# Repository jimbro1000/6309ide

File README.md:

# 8 Bit IDE for 6309 SBC #

Inspired (and partially copied from) Breadbording Labs 
(https://www.youtube.com/@breadboardinglabs) which is,
in turn, taken from other existing 8 bit IDE projects.

This design is configured to work with my 6309 SBC 
project.

## Status ##

This is a work in progress and is not ready for production.
The two SEL lines are not wired and need some address selection
logic to fit the design to the available mapped memory

## Drivers ##

The IDE operation requires software drivers to simplify
operation. It also needs programming for the GAL

### GAL Definition ###

Input (1-9):  
A0, A4, A5, A6, A6, E, SEL0, RW, SEL1

Output (19-12):  
!UDW, !UDR, !LDW, !IOW, !IOR, !CS0, !CS1, !LDR

ACT = !A5 & !A6 & !A7 & !SEL0

CS0 = !A4 & ACT  
CS1 = A4 & ACT  
IOR = !A0 & ACT & RW  
IOW = A0 & ACT & !RW  
LDR = !A0 & ACT & RW  
LDW = !A0 & ACT & !RW  
UDR = A0 & ACT & RW  
UDW = A0 & ACT & !RW

(note: IOR and LDR are the same)

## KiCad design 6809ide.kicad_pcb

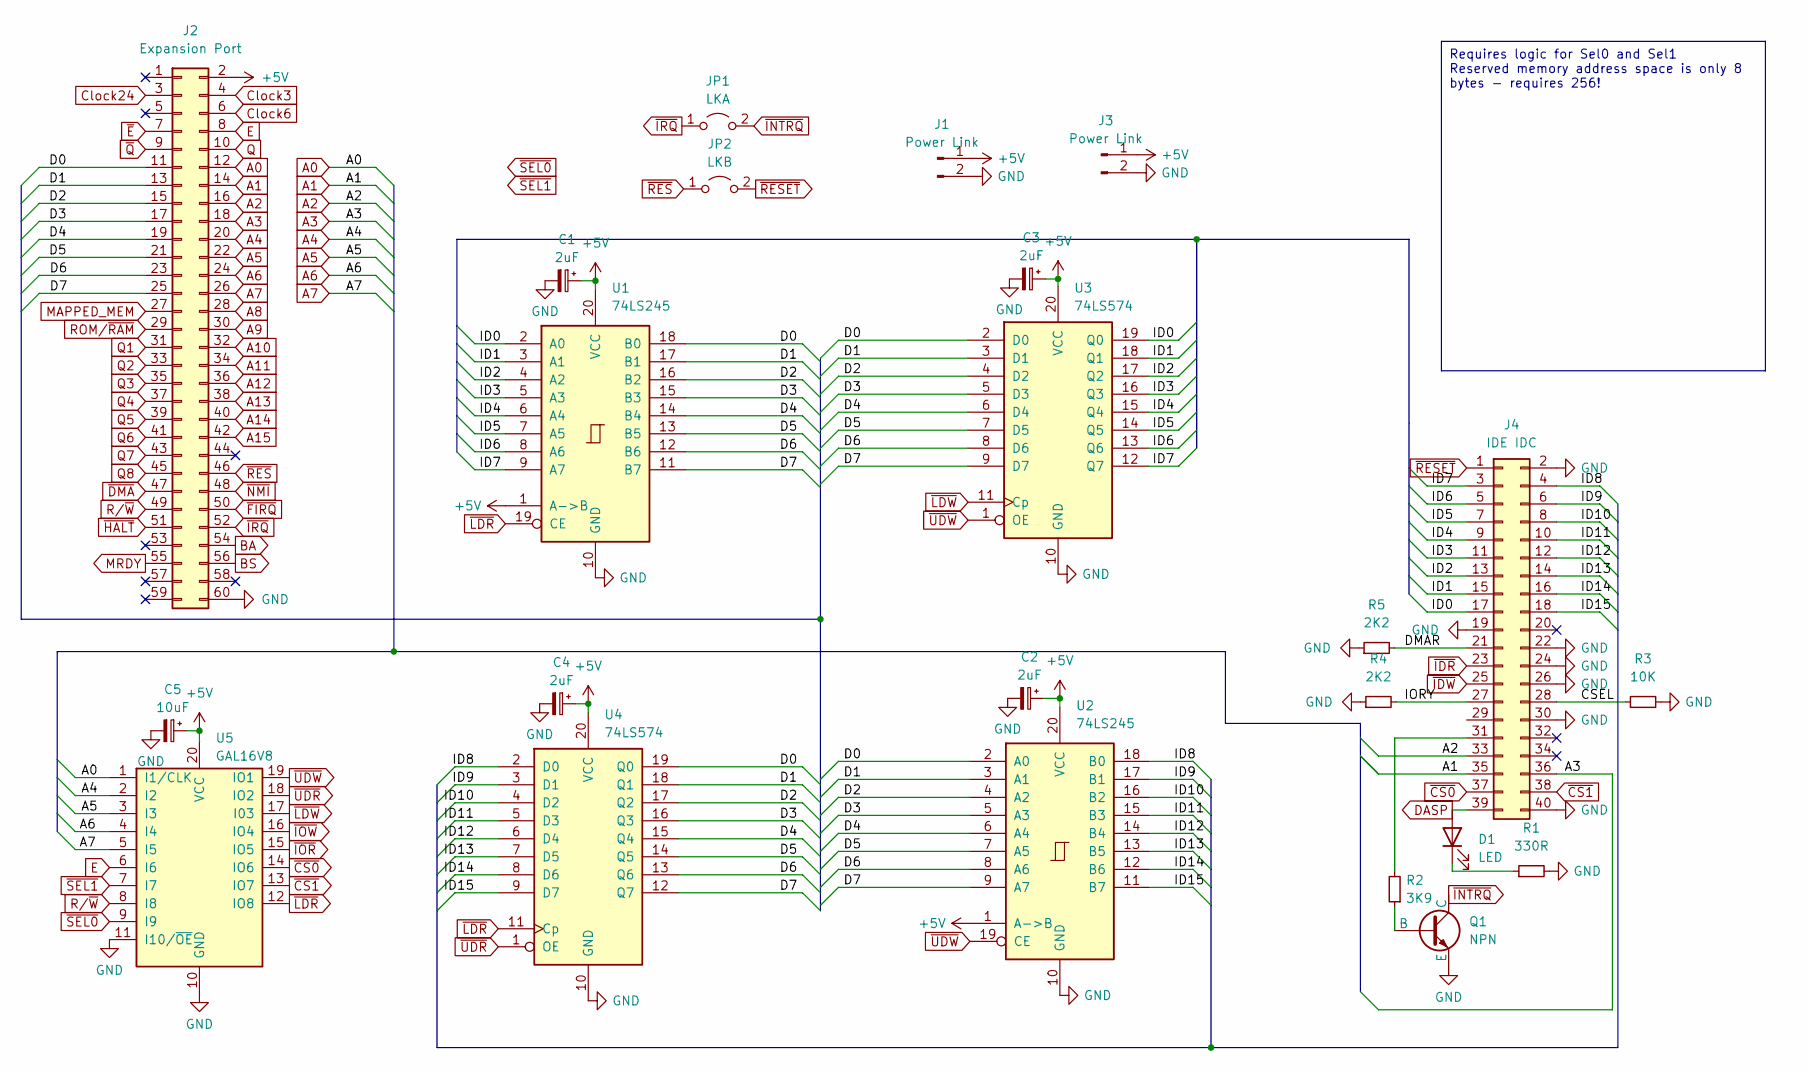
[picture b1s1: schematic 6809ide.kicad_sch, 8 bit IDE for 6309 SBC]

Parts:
C1, C2, C3, C4: 2uF; CP_Elec_4x3
C5: 10uF; CP_Elec_6.3x3
D1: LED; LED_0805_2012Metric_Pad1.15x1.40mm_HandSolder
J1, J3: Power Link; PinHeader_1x02_P2.54mm_Vertical
J2: Expansion Port; PinHeader_2x30_P2.54mm_Vertical
J4: IDE IDC; IDC-Header_2x20_P2.54mm_Vertical
JP1: LKA; SolderJumper-2_P1.3mm_Open_RoundedPad1.0x1.5mm
JP2: LKB; SolderJumper-2_P1.3mm_Open_RoundedPad1.0x1.5mm
Q1: NPN; SOT-23-3
R1: 330R; R_0805_2012Metric_Pad1.20x1.40mm_HandSolder
R2: 3K9; R_0805_2012Metric_Pad1.20x1.40mm_HandSolder
R3: 10K; R_0805_2012Metric_Pad1.20x1.40mm_HandSolder
R4, R5: 2K2; R_0805_2012Metric_Pad1.20x1.40mm_HandSolder
U1, U2: 74LS245; SOIC-20W_7.5x12.8mm_P1.27mm
U3, U4: 74LS574; SOIC-20W_7.5x12.8mm_P1.27mm
U5: GAL16V8; SOIC-20W_7.5x12.8mm_P1.27mm

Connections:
+5V: C1.1, C2.1, C3.1, C4.1, C5.1, J1.1, J2.2, J3.1, U1.1 (A->B), U1.20 (VCC), U2.1 (A->B), U2.20 (VCC), U3.20 (VCC), U4.20 (VCC), U5.20 (VCC)
/CSEL: J4.28, R3.1
/D0: J2.11, U1.18 (B0), U2.2 (A0), U3.2 (D0), U4.19 (Q0)
/D1: J2.13, U1.17 (B1), U2.3 (A1), U3.3 (D1), U4.18 (Q1)
/D2: J2.15, U1.16 (B2), U2.4 (A2), U3.4 (D2), U4.17 (Q2)
/D3: J2.17, U1.15 (B3), U2.5 (A3), U3.5 (D3), U4.16 (Q3)
/D4: J2.19, U1.14 (B4), U2.6 (A4), U3.6 (D4), U4.15 (Q4)
/D5: J2.21, U1.13 (B5), U2.7 (A5), U3.7 (D5), U4.14 (Q5)
/D6: J2.23, U1.12 (B6), U2.8 (A6), U3.8 (D6), U4.13 (Q6)
/D7: J2.25, U1.11 (B7), U2.9 (A7), U3.9 (D7), U4.12 (Q7)
/DMAR: J4.21, R5.2
/ID0: J4.17, U1.2 (A0), U3.19 (Q0)
/ID1: J4.15, U1.3 (A1), U3.18 (Q1)
/ID2: J4.13, U1.4 (A2), U3.17 (Q2)
/ID3: J4.11, U1.5 (A3), U3.16 (Q3)
/ID4: J4.9, U1.6 (A4), U3.15 (Q4)
/ID5: J4.7, U1.7 (A5), U3.14 (Q5)
/ID6: J4.5, U1.8 (A6), U3.13 (Q6)
/ID7: J4.3, U1.9 (A7), U3.12 (Q7)
/ID8: J4.4, U2.18 (B0), U4.2 (D0)
/ID9: J4.6, U2.17 (B1), U4.3 (D1)
/ID10: J4.8, U2.16 (B2), U4.4 (D2)
/ID11: J4.10, U2.15 (B3), U4.5 (D3)
/ID12: J4.12, U2.14 (B4), U4.6 (D4)
/ID13: J4.14, U2.13 (B5), U4.7 (D5)
/ID14: J4.16, U2.12 (B6), U4.8 (D6)
/ID15: J4.18, U2.11 (B7), U4.9 (D7)
/IORY: J4.27, R4.2
A0: J2.12, U5.1 (I1/CLK)
A1: J2.14, J4.35
A2: J2.16, J4.33
A3: J2.18, J4.36
A4: J2.20, U5.2 (I2)
A5: J2.22, U5.3 (I3)
A6: J2.24, U5.4 (I4)
A7: J2.26, U5.5 (I5)
A8: J2.28
A9: J2.30
A10: J2.32
A11: J2.34
A12: J2.36
A13: J2.38
A14: J2.40
A15: J2.42
BA: J2.54
BS: J2.56
Clock3: J2.4
Clock6: J2.6
Clock24: J2.3
DASP: D1.2 (A), J4.39
E: J2.8, U5.6 (I6)
GND: C1.2, C2.2, C3.2, C4.2, C5.2, J1.2, J2.60, J3.2, J4.2, J4.19, J4.22, J4.24, J4.26, J4.30, J4.40, Q1.3 (E), R1.2, R3.2, R4.1, R5.1, U1.10 (GND), U2.10 (GND), U3.10 (GND), U4.10 (GND), U5.10 (GND), U5.11 (I10/~OE)
MAPPED_MEM: J2.27
MRDY: J2.55
unnamed: D1.1 (K), R1.1
unnamed: J4.31, R2.2
unnamed: Q1.2 (B), R2.1
Q: J2.10
Q1: J2.31
Q2: J2.33
Q3: J2.35
Q4: J2.37
Q5: J2.39
Q6: J2.41
Q7: J2.43
Q8: J2.45
ROM/~RAM: J2.29
R/~W: J2.49, U5.8 (I8)
~CS0: J4.37, U5.14 (IO6)
~CS1: J4.38, U5.13 (IO7)
~DMA: J2.47
~E: J2.7
~FIRQ: J2.50
~HALT: J2.51
~IDR: J4.23
~IDW: J4.25
~INTRQ: JP1.2 (B), Q1.1 (C)
~IOR: U5.15 (IO5)
~IOW: U5.16 (IO4)
~IRQ: J2.52, JP1.1 (A)
~LDR: U1.19 (CE), U4.11 (Cp), U5.12 (IO8)
~LDW: U3.11 (Cp), U5.17 (I03)
~NMI: J2.48
~Q: J2.9
~RESET: J4.1, JP2.2 (B)
~RES: J2.46, JP2.1 (A)
~SEL0: U5.9 (I9)
~SEL1: U5.7 (I7)
~UDR: U4.1 (OE), U5.18 (IO2)
~UDW: U2.19 (CE), U3.1 (OE), U5.19 (IO1)

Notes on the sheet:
Requires logic for Sel0 and Sel1 Reserved memory address space is only 8 bytes - requires 256!

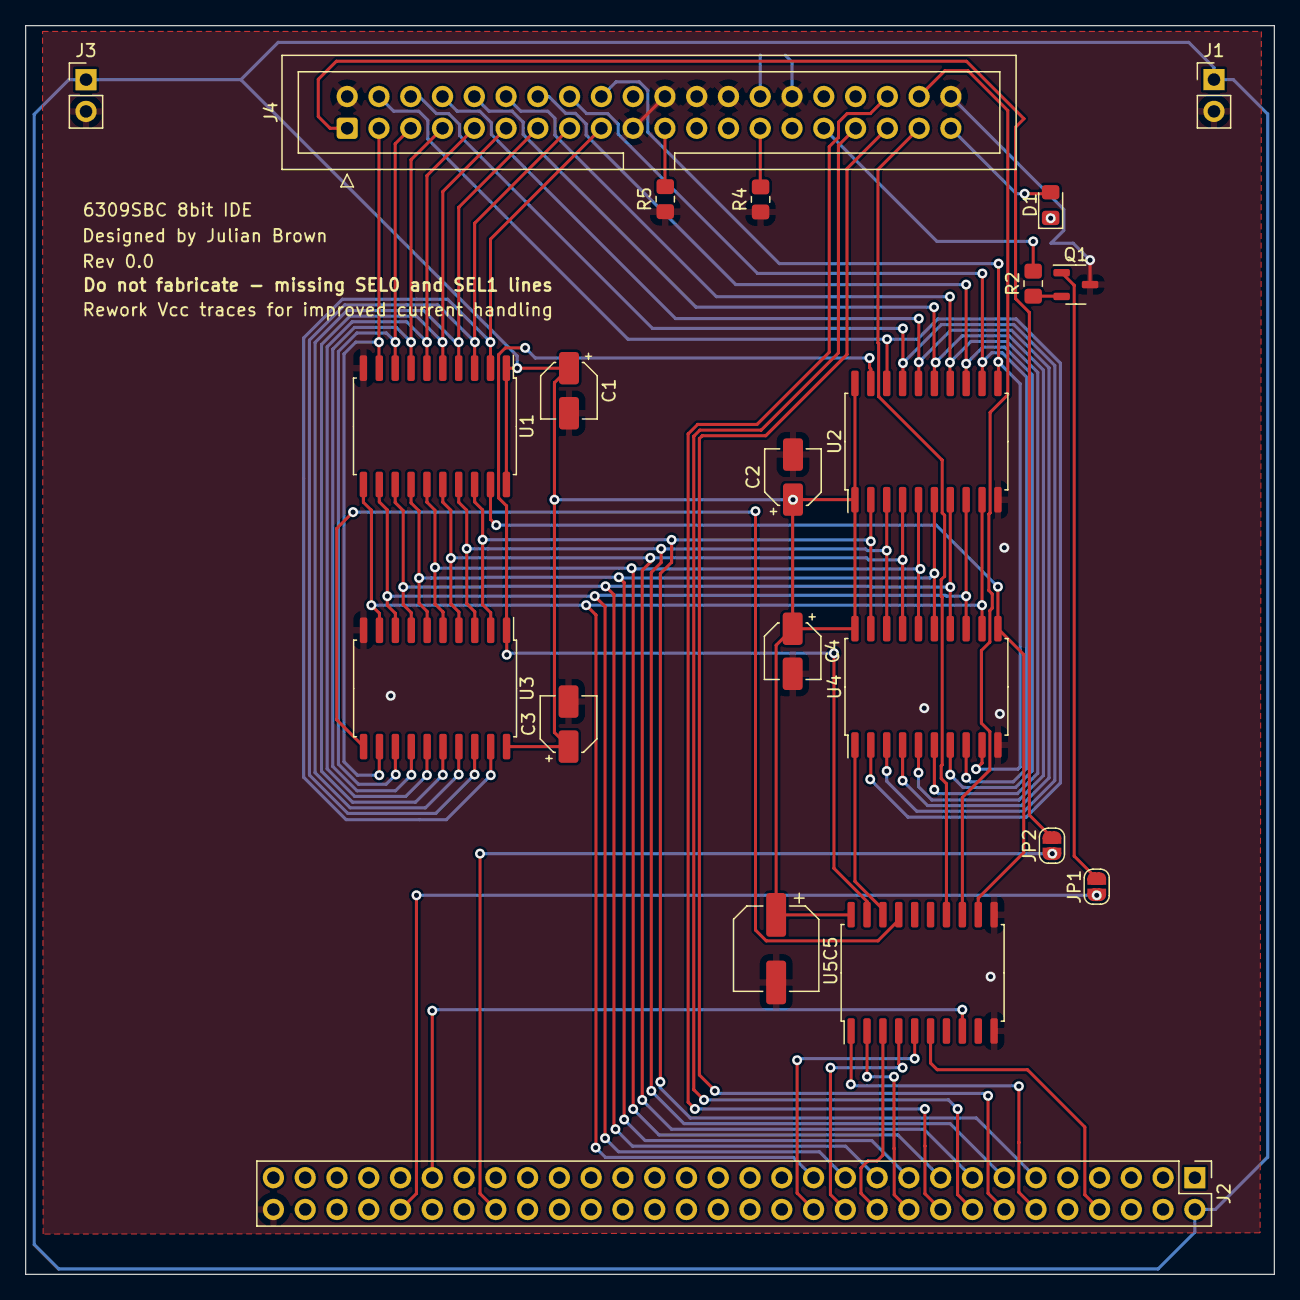
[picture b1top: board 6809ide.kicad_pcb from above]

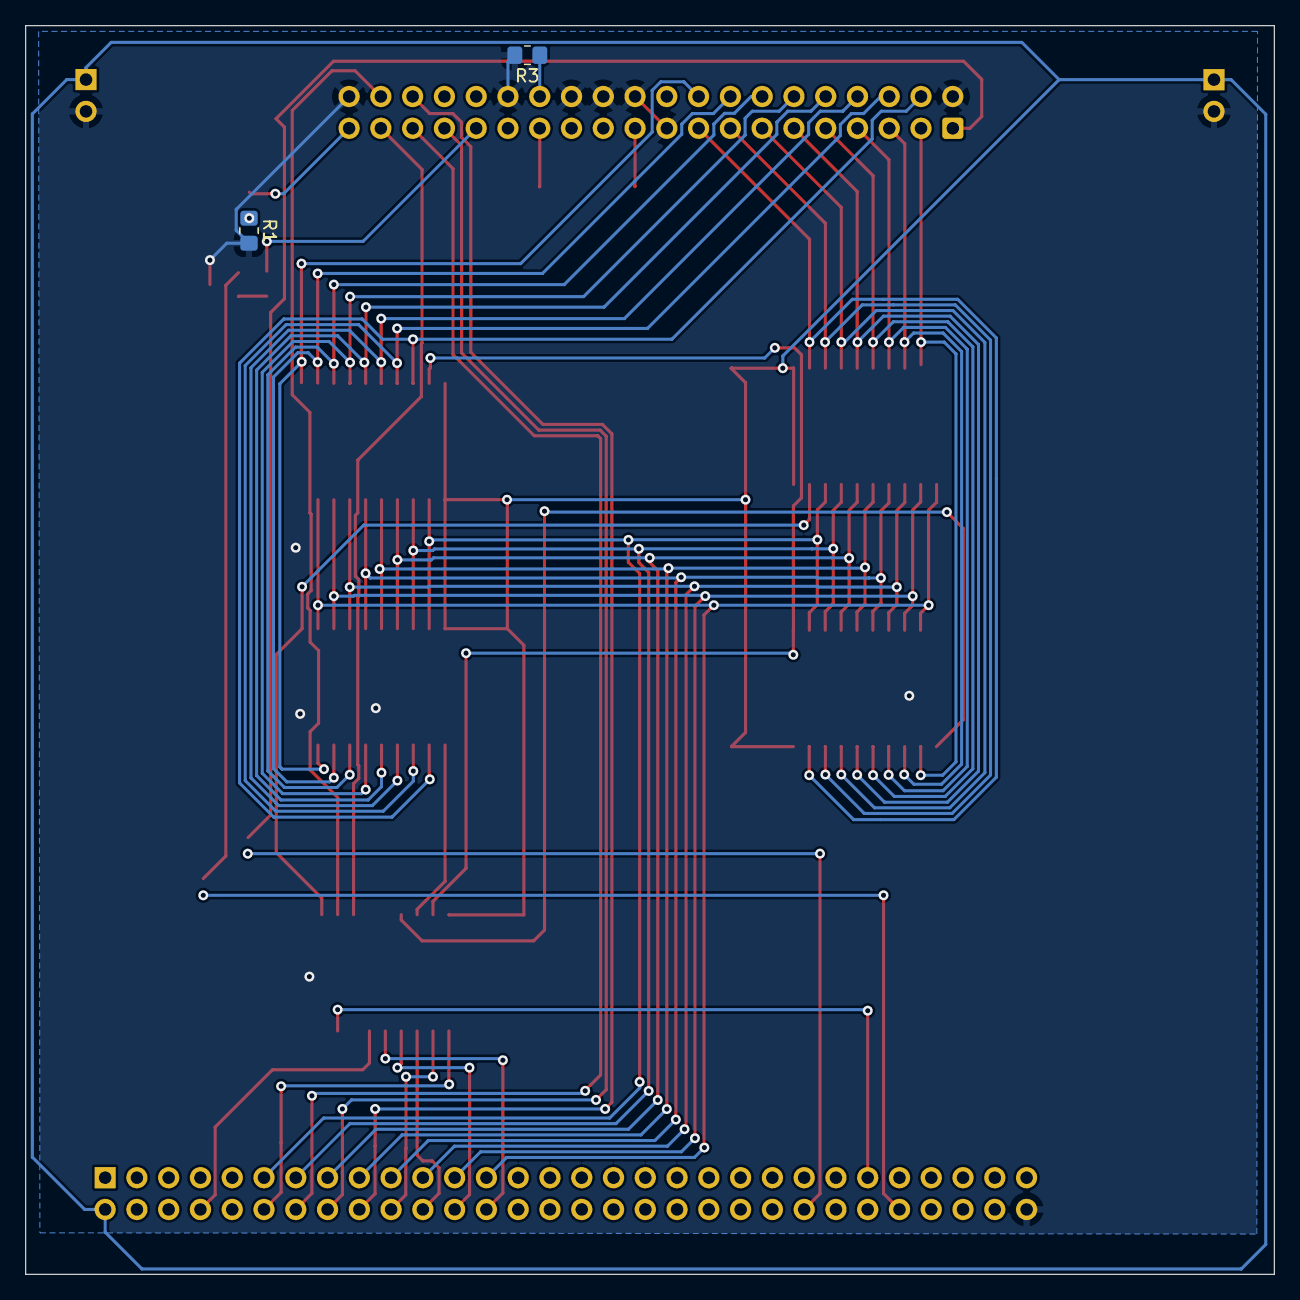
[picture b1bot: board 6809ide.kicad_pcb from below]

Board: 2 copper layers, 99.8 x 99.8 mm, 23 parts (2 on the bottom side), 53 nets.
